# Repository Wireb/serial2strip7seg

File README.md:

### Serial to dual 7 segment display led strip driver

This driver is a serial input to dual 7 segment display driver. 

####Inputs:
Synchronous serial input signals 
  Data in
  Serial clock
  Reset
  Latch data
  
####Outputs:
Synchronous serial outputs signals 
  Data out
  Serial clock
  Reset
  Latch data
LED strip outputs
  14x 2.3A @ 20V max (not including thermal limits)
  
####Power:
Logic and serial intputs/outputs can be run off 3.3V or 5V   
LED side only needs a ground connection
!!NOTE!! logic and led grounds are connected. Make sure the LED grounds are large enough to carry all the current of the LED strips. Also watch out for ground loops.

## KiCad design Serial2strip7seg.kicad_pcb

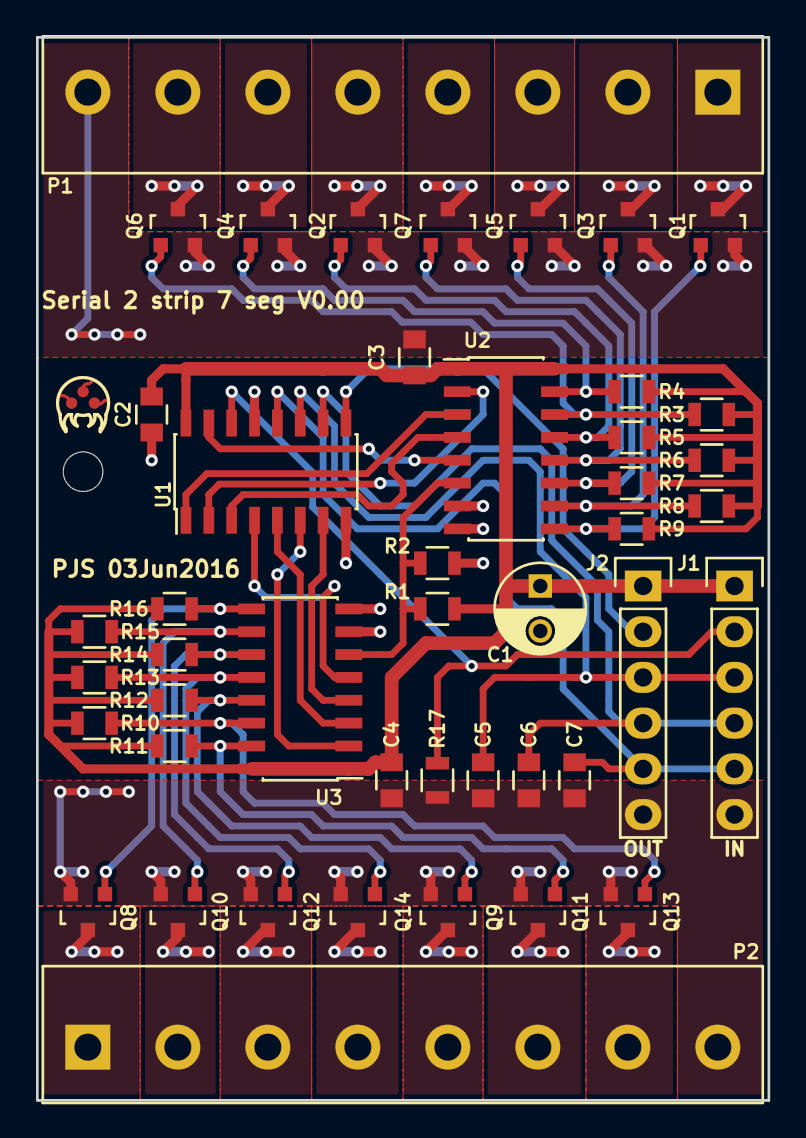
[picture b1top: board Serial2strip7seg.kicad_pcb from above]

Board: 2 copper layers, 40.6 x 59.1 mm, 46 parts (0 on the bottom side), 44 nets.

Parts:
C1: 100uF; C_Radial_D5_L11_P2.5
C2, C3, C4: 0.1uF; C_0805
C5, C6, C7: no_pop; C_0805
J1, J2: pin_header; Pin_Header_Straight_1x06
P1, P2: Screw terminals; DG301-5.008P-12
Q1, Q2, Q3, Q4, Q5, Q6, Q7, Q8, Q9, Q10, Q11, Q12, Q13, Q14: BSS806N; SOT-23
R1, R3, R4, R5, R6, R7, R8, R9, R10, R11, R12, R13, R14, R15, R16, R17: 10k; R_0805
R2: no_pop; R_0805
U1: 74HC595a; SOIC-16_3.9x9.9mm_Pitch1.27mm
U2, U3: CD4056; SOIC-16_3.9x9.9mm_Pitch1.27mm
icon1: Metroid; metroid

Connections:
GND: C1.2, C2.2, C3.2, C4.2, C5.2, C6.2, C7.2, J1.6, J2.6, P1.8, P2.8, Q1.2, Q2.2, Q3.2, Q4.2, Q5.2, Q6.2, Q7.2, Q8.2, Q9.2, Q10.2, Q11.2, Q12.2, Q13.2, Q14.2, R2.2, R17.2, U1.8, U1.13, U2.7, U2.8, U3.7, U3.8
unnamed: C5.1, J1.3, J2.3, U1.11
unnamed: C6.1, J1.4, J2.4, U1.10
unnamed: C7.1, J1.5, J2.5, U1.12
unnamed: J1.2, R17.1, U1.14
unnamed: J2.2, U1.9
unnamed: P1.1, Q1.3
unnamed: P1.2, Q3.3
unnamed: P1.3, Q5.3
unnamed: P1.4, Q7.3
unnamed: P1.5, Q2.3
unnamed: P1.6, Q4.3
unnamed: P1.7, Q6.3
unnamed: P2.1, Q8.3
unnamed: P2.2, Q10.3
unnamed: P2.3, Q12.3
unnamed: P2.4, Q14.3
unnamed: P2.5, Q9.3
unnamed: P2.6, Q11.3
unnamed: P2.7, Q13.3
unnamed: Q1.1, R9.2, U2.9
unnamed: Q2.1, R5.2, U2.13
unnamed: Q3.1, R8.2, U2.10
unnamed: Q4.1, R4.2, U2.15
unnamed: Q5.1, R7.2, U2.11
unnamed: Q6.1, R3.2, U2.14
unnamed: Q7.1, R6.2, U2.12
unnamed: Q8.1, R16.2, U3.9
unnamed: Q9.1, R12.2, U3.13
unnamed: Q10.1, R15.2, U3.10
unnamed: Q11.1, R11.2, U3.15
unnamed: Q12.1, R14.2, U3.11
unnamed: Q13.1, R10.2, U3.14
unnamed: Q14.1, R13.2, U3.12
unnamed: R1.2, R2.1, U2.6, U3.6
unnamed: U1.1, U2.3
unnamed: U1.2, U2.2
unnamed: U1.3, U2.4
unnamed: U1.4, U3.5
unnamed: U1.5, U3.3
unnamed: U1.6, U3.2
unnamed: U1.7, U3.4
unnamed: U1.15, U2.5
VCC: C1.1, C2.1, C3.1, C4.1, J1.1, J2.1, R1.1, R3.1, R4.1, R5.1, R6.1, R7.1, R8.1, R9.1, R10.1, R11.1, R12.1, R13.1, R14.1, R15.1, R16.1, U1.16, U2.1, U2.16, U3.1, U3.16

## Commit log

2016-06-04 :space_invader: Added .gitattributes & .gitignore files
2016-06-04 first upload

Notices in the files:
Serial2strip7seg.kicad_pcb:
Copyright (c) 2016 Peter Shabino
